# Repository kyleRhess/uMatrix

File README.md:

# MicroMatrix (uMatrix)

## uMatrix is an Arduino library for controlling a custom 16x8 LED matrix display

\
This library uses the built-in SPI peripheral to communicate with a set of shift registers and the LED matrix. The existing library currently relies on custom hardware, but could be tailored to other designs.

\

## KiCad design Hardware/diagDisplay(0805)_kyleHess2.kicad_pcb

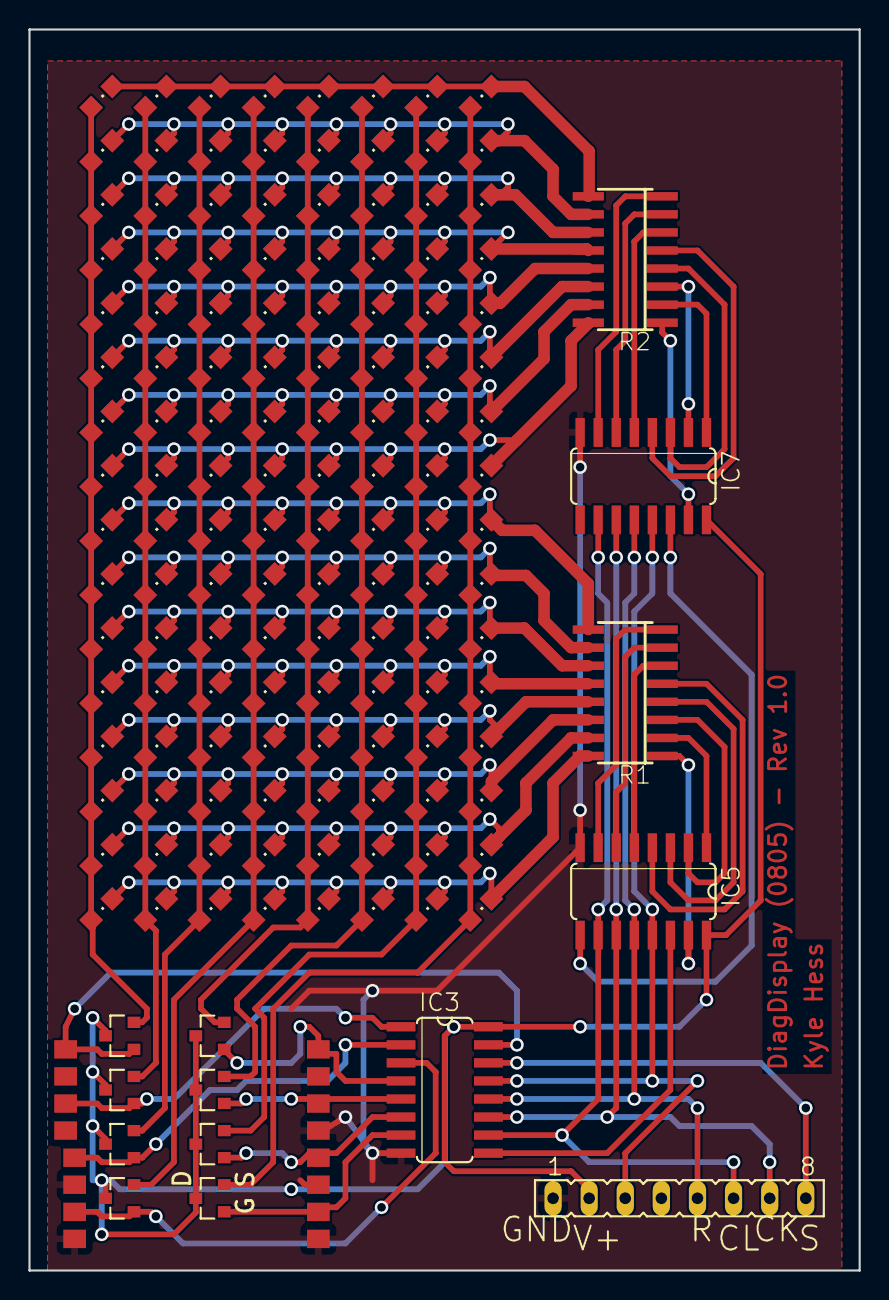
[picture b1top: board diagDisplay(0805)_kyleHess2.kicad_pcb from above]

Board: 2 copper layers, 58.4 x 87.3 mm, 150 parts (0 on the bottom side), 57 nets.

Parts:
IC3, IC5, IC7: 74595D; SO16
LED1, LED2, LED3, LED4, LED5, LED6, LED7, LED8, LED9, LED10, LED11, LED12, LED13, LED14, LED15, LED16, LED17, LED18, LED19, LED20, LED21, LED22, LED23, LED24, LED25, LED26, LED27, LED28, LED29, LED30, LED31, LED32, LED33, LED34, LED35, LED36, LED37, LED38, LED39, LED40, LED41, LED42, LED43, LED44, LED45, LED46, LED47, LED48, LED49, LED50, LED51, LED52, LED53, LED54, LED55, LED56, LED57, LED58, LED59, LED60, LED61, LED62, LED63, LED64, LED65, LED66, LED67, LED68, LED69, LED70, LED71, LED72, LED73, LED74, LED75, LED76, LED77, LED78, LED79, LED80, LED81, LED82, LED83, LED84, LED85, LED86, LED87, LED88, LED89, LED90, LED91, LED92, LED93, LED94, LED95, LED96, LED97, LED98, LED99, LED100, LED101, LED102, LED103, LED104, LED105, LED106, LED107, LED108, LED109, LED110, LED111, LED112, LED113, LED114, LED115, LED116, LED117, LED118, LED119, LED120, LED121, LED122, LED123, LED124, LED125, LED126, LED127, LED128: LEDCHIPLED_0805; CHIPLED_0805
R1, R2: 2NBS16-8; SO16
R3, R4, R5, R6, R7, R8, R9, R10: R-US_M0805; M0805
SV1: FE08-1; FE08
U$1, U$2, U$3, U$4, U$5, U$6, U$7, U$8: N-CHANNEL-MOSFET-BSS138; SOT23-3

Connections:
/PWM: IC3.13, IC5.13, IC7.13, SV1.3
/RCK: IC3.12, IC5.12, IC7.12, SV1.5
/SCK: IC3.11, IC5.11, IC7.11, SV1.7
/SCL: IC3.10, IC5.10, IC7.10, SV1.6
/SER: IC3.14, SV1.8
/VSUP: IC3.16, IC5.16, IC7.16, SV1.2, U$1.3, U$2.3, U$3.3, U$4.3, U$5.3, U$6.3, U$7.3, U$8.3
GND: IC3.8, IC5.8, IC7.8, R3.1, R4.1, R5.1, R6.1, R7.1, R8.1, R9.1, R10.1, SV1.1
unnamed: IC3.1, R4.2, U$2.1
unnamed: IC3.2, R5.2, U$3.1
unnamed: IC3.3, R6.2, U$4.1
unnamed: IC3.4, R7.2, U$5.1
unnamed: IC3.5, R8.2, U$6.1
unnamed: IC3.6, R9.2, U$7.1
unnamed: IC3.7, R10.2, U$8.1
unnamed: IC3.9, IC5.14
unnamed: IC3.15, R3.2, U$1.1
unnamed: IC5.1, R1.2
unnamed: IC5.2, R1.3
unnamed: IC5.3, R1.4
unnamed: IC5.4, R1.5
unnamed: IC5.5, R1.6
unnamed: IC5.6, R1.7
unnamed: IC5.7, R1.8
unnamed: IC5.9, IC7.14
unnamed: IC5.15, R1.1
unnamed: IC7.1, R2.2
unnamed: IC7.2, R2.3
unnamed: IC7.3, R2.4
unnamed: IC7.4, R2.5
unnamed: IC7.5, R2.6
unnamed: IC7.6, R2.7
unnamed: IC7.7, R2.8
unnamed: IC7.15, R2.1
unnamed: LED1.A, LED9.A, LED17.A, LED25.A, LED33.A, LED41.A, LED49.A, LED57.A, LED65.A, LED73.A, LED81.A, LED89.A, LED97.A, LED105.A, LED113.A, LED121.A, U$1.2
unnamed: LED1.C, LED2.C, LED3.C, LED4.C, LED5.C, LED6.C, LED7.C, LED8.C, R1.16
unnamed: LED2.A, LED10.A, LED18.A, LED26.A, LED34.A, LED42.A, LED50.A, LED58.A, LED66.A, LED74.A, LED82.A, LED90.A, LED98.A, LED106.A, LED114.A, LED122.A, U$2.2
unnamed: LED9.C, LED10.C, LED11.C, LED12.C, LED13.C, LED14.C, LED15.C, LED16.C, R1.15
unnamed: LED17.C, LED18.C, LED19.C, LED20.C, LED21.C, LED22.C, LED23.C, LED24.C, R1.14
unnamed: LED25.C, LED26.C, LED27.C, LED28.C, LED29.C, LED30.C, LED31.C, LED32.C, R1.13
unnamed: LED33.C, LED34.C, LED35.C, LED36.C, LED37.C, LED38.C, LED39.C, LED40.C, R1.12
unnamed: LED41.C, LED42.C, LED43.C, LED44.C, LED45.C, LED46.C, LED47.C, LED48.C, R1.11
unnamed: LED49.C, LED50.C, LED51.C, LED52.C, LED53.C, LED54.C, LED55.C, LED56.C, R1.10
unnamed: LED57.C, LED58.C, LED59.C, LED60.C, LED61.C, LED62.C, LED63.C, LED64.C, R1.9
unnamed: LED65.C, LED66.C, LED67.C, LED68.C, LED69.C, LED70.C, LED71.C, LED72.C, R2.16
unnamed: LED73.C, LED74.C, LED75.C, LED76.C, LED77.C, LED78.C, LED79.C, LED80.C, R2.15
unnamed: LED81.C, LED82.C, LED83.C, LED84.C, LED85.C, LED86.C, LED87.C, LED88.C, R2.14
unnamed: LED89.C, LED90.C, LED91.C, LED92.C, LED93.C, LED94.C, LED95.C, LED96.C, R2.13
unnamed: LED4.A, LED12.A, LED20.A, LED28.A, LED36.A, LED44.A, LED52.A, LED60.A, LED68.A, LED76.A, LED84.A, LED92.A, LED100.A, LED108.A, LED116.A, LED124.A, U$4.2
unnamed: LED97.C, LED98.C, LED99.C, LED100.C, LED101.C, LED102.C, LED103.C, LED104.C, R2.12
unnamed: LED5.A, LED13.A, LED21.A, LED29.A, LED37.A, LED45.A, LED53.A, LED61.A, LED69.A, LED77.A, LED85.A, LED93.A, LED101.A, LED109.A, LED117.A, LED125.A, U$5.2
unnamed: LED6.A, LED14.A, LED22.A, LED30.A, LED38.A, LED46.A, LED54.A, LED62.A, LED70.A, LED78.A, LED86.A, LED94.A, LED102.A, LED110.A, LED118.A, LED126.A, U$6.2
unnamed: LED7.A, LED15.A, LED23.A, LED31.A, LED39.A, LED47.A, LED55.A, LED63.A, LED71.A, LED79.A, LED87.A, LED95.A, LED103.A, LED111.A, LED119.A, LED127.A, U$7.2
unnamed: LED8.A, LED16.A, LED24.A, LED32.A, LED40.A, LED48.A, LED56.A, LED64.A, LED72.A, LED80.A, LED88.A, LED96.A, LED104.A, LED112.A, LED120.A, LED128.A, U$8.2
unnamed: LED105.C, LED106.C, LED107.C, LED108.C, LED109.C, LED110.C, LED111.C, LED112.C, R2.11
unnamed: LED3.A, LED11.A, LED19.A, LED27.A, LED35.A, LED43.A, LED51.A, LED59.A, LED67.A, LED75.A, LED83.A, LED91.A, LED99.A, LED107.A, LED115.A, LED123.A, U$3.2
unnamed: LED113.C, LED114.C, LED115.C, LED116.C, LED117.C, LED118.C, LED119.C, LED120.C, R2.10
unnamed: LED121.C, LED122.C, LED123.C, LED124.C, LED125.C, LED126.C, LED127.C, LED128.C, R2.9

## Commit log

2020-01-25 Removed unnecessary files and added two example files (GOL, Fade).
2020-01-25 Added hardware files.
2020-01-27 Updated hardware to use latest library references.
